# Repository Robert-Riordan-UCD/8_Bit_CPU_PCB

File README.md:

# 8-Bit PCB CPU

This is my version of [Ben Eaters 8-bit breadboard SAP-1 CPU](https://eater.net/8bit), converted to a PCB. I have made some minor changes as I could not find all of the components as listed in Ben's part list.

## Video of the computer running
https://youtube.com/shorts/QNcSWgcGv9o?si=QzoUVq9Kj8X1f4Rs

## Major Changes

### Random Access Memory

1. RAM IC's have been replaced with ATMega328-PU's. This should allow me to have persistant programs between power cycles.

## License

CERN Open Hardware Licence Version 2 - Permissive

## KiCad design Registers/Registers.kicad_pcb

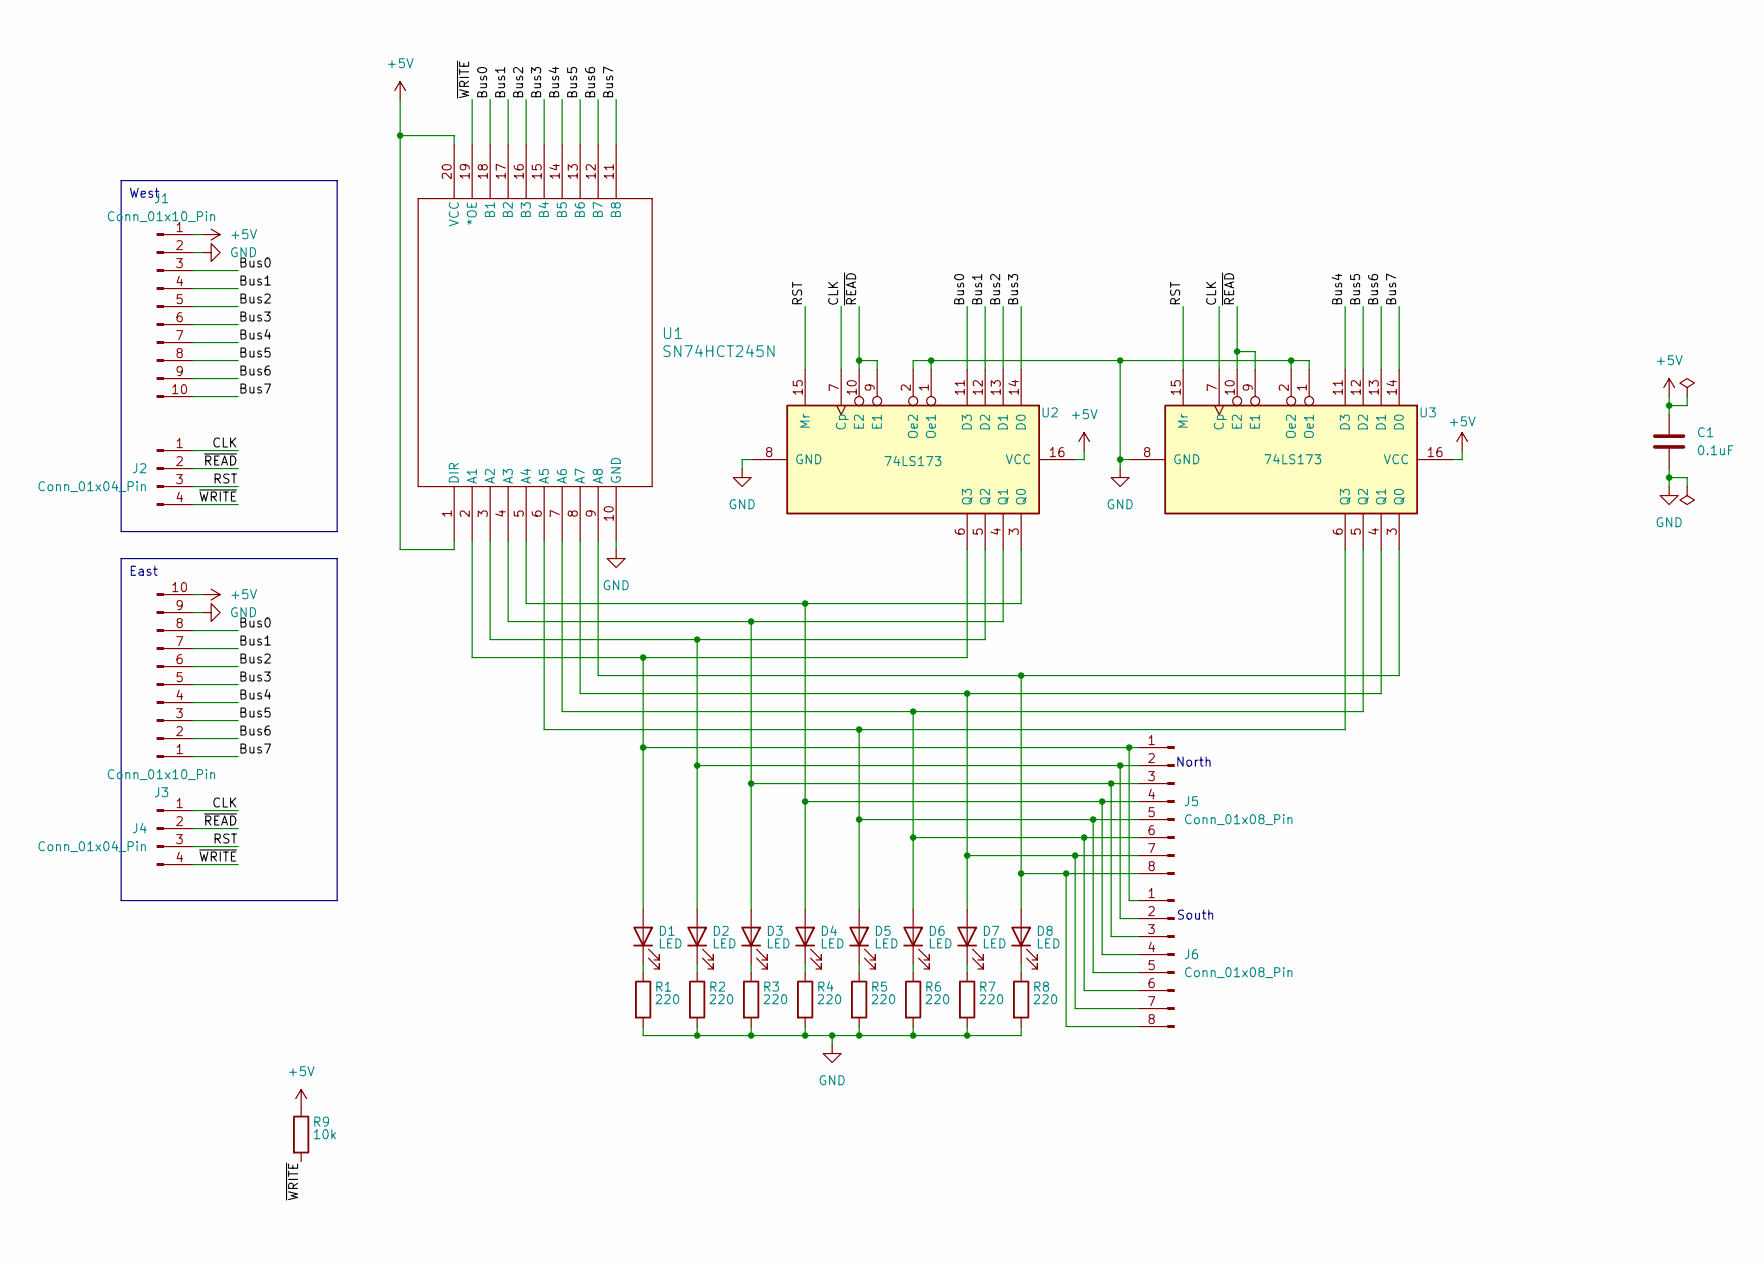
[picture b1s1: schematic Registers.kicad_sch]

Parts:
C1: 0.1uF; C_Disc_D5.0mm_W2.5mm_P2.50mm
D1, D2, D3, D4, D5, D6, D7, D8: LED; LED_D5.0mm
J1, J3: Conn_01x10_Pin; PinHeader_1x10_P2.54mm_Vertical
J2, J4: Conn_01x04_Pin; PinHeader_1x04_P2.54mm_Vertical
J5, J6: Conn_01x08_Pin; PinHeader_1x08_P2.54mm_Vertical
R1, R2, R3, R4, R5, R6, R7, R8: 220; CF_series_Resistors_THT
R9: 10k; CF_series_Resistors_THT
U1: SN74HCT245N; 8x_tristate_transceiver
U2, U3: 74LS173; DIP-16_W7.62mm

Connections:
+5V: C1.1, J1.1, J3.10, R9.1, U1.1 (DIR), U1.20 (VCC), U2.16 (VCC), U3.16 (VCC)
/Bus0: J1.3, J3.8, U1.18 (B1), U2.11 (D3)
/Bus1: J1.4, J3.7, U1.17 (B2), U2.12 (D2)
/Bus2: J1.5, J3.6, U1.16 (B3), U2.13 (D1)
/Bus3: J1.6, J3.5, U1.15 (B4), U2.14 (D0)
/Bus4: J1.7, J3.4, U1.14 (B5), U3.11 (D3)
/Bus5: J1.8, J3.3, U1.13 (B6), U3.12 (D2)
/Bus6: J1.9, J3.2, U1.12 (B7), U3.13 (D1)
/Bus7: J1.10, J3.1, U1.11 (B8), U3.14 (D0)
/CLK: J2.1, J4.1, U2.7 (Cp), U3.7 (Cp)
/RST: J2.3, J4.3, U2.15 (Mr), U3.15 (Mr)
/~READ: J2.2, J4.2, U2.9 (E1), U2.10 (E2), U3.9 (E1), U3.10 (E2)
/~WRITE: J2.4, J4.4, R9.2, U1.19 (*OE)
GND: C1.2, J1.2, J3.9, R1.2, R2.2, R3.2, R4.2, R5.2, R6.2, R7.2, R8.2, U1.10 (GND), U2.1 (Oe1), U2.2 (Oe2), U2.8 (GND), U3.1 (Oe1), U3.2 (Oe2), U3.8 (GND)
unnamed: D1.2 (A), J5.1, J6.1, U1.2 (A1), U2.6 (Q3)
unnamed: D1.1 (K), R1.1
unnamed: D2.2 (A), J5.2, J6.2, U1.3 (A2), U2.5 (Q2)
unnamed: D2.1 (K), R2.1
unnamed: D3.2 (A), J5.3, J6.3, U1.4 (A3), U2.4 (Q1)
unnamed: D3.1 (K), R3.1
unnamed: D4.2 (A), J5.4, J6.4, U1.5 (A4), U2.3 (Q0)
unnamed: D4.1 (K), R4.1
unnamed: D5.2 (A), J5.5, J6.5, U1.6 (A5), U3.6 (Q3)
unnamed: D5.1 (K), R5.1
unnamed: D6.2 (A), J5.6, J6.6, U1.7 (A6), U3.5 (Q2)
unnamed: D6.1 (K), R6.1
unnamed: D7.2 (A), J5.7, J6.7, U1.8 (A7), U3.4 (Q1)
unnamed: D7.1 (K), R7.1
unnamed: D8.2 (A), J5.8, J6.8, U1.9 (A8), U3.3 (Q0)
unnamed: D8.1 (K), R8.1

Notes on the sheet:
West
East
North
South

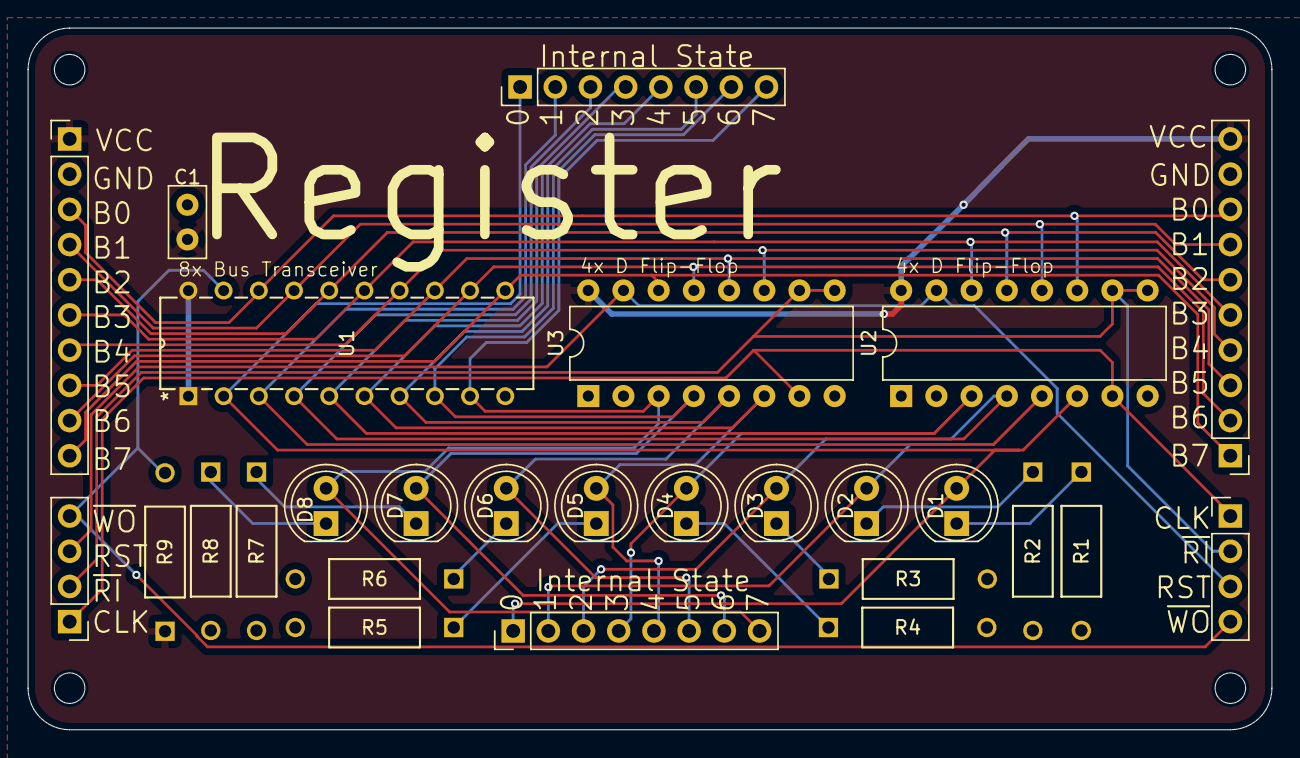
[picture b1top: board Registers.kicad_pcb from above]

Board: 2 copper layers, 89.8 x 50.6 mm, 27 parts (0 on the bottom side), 30 nets.

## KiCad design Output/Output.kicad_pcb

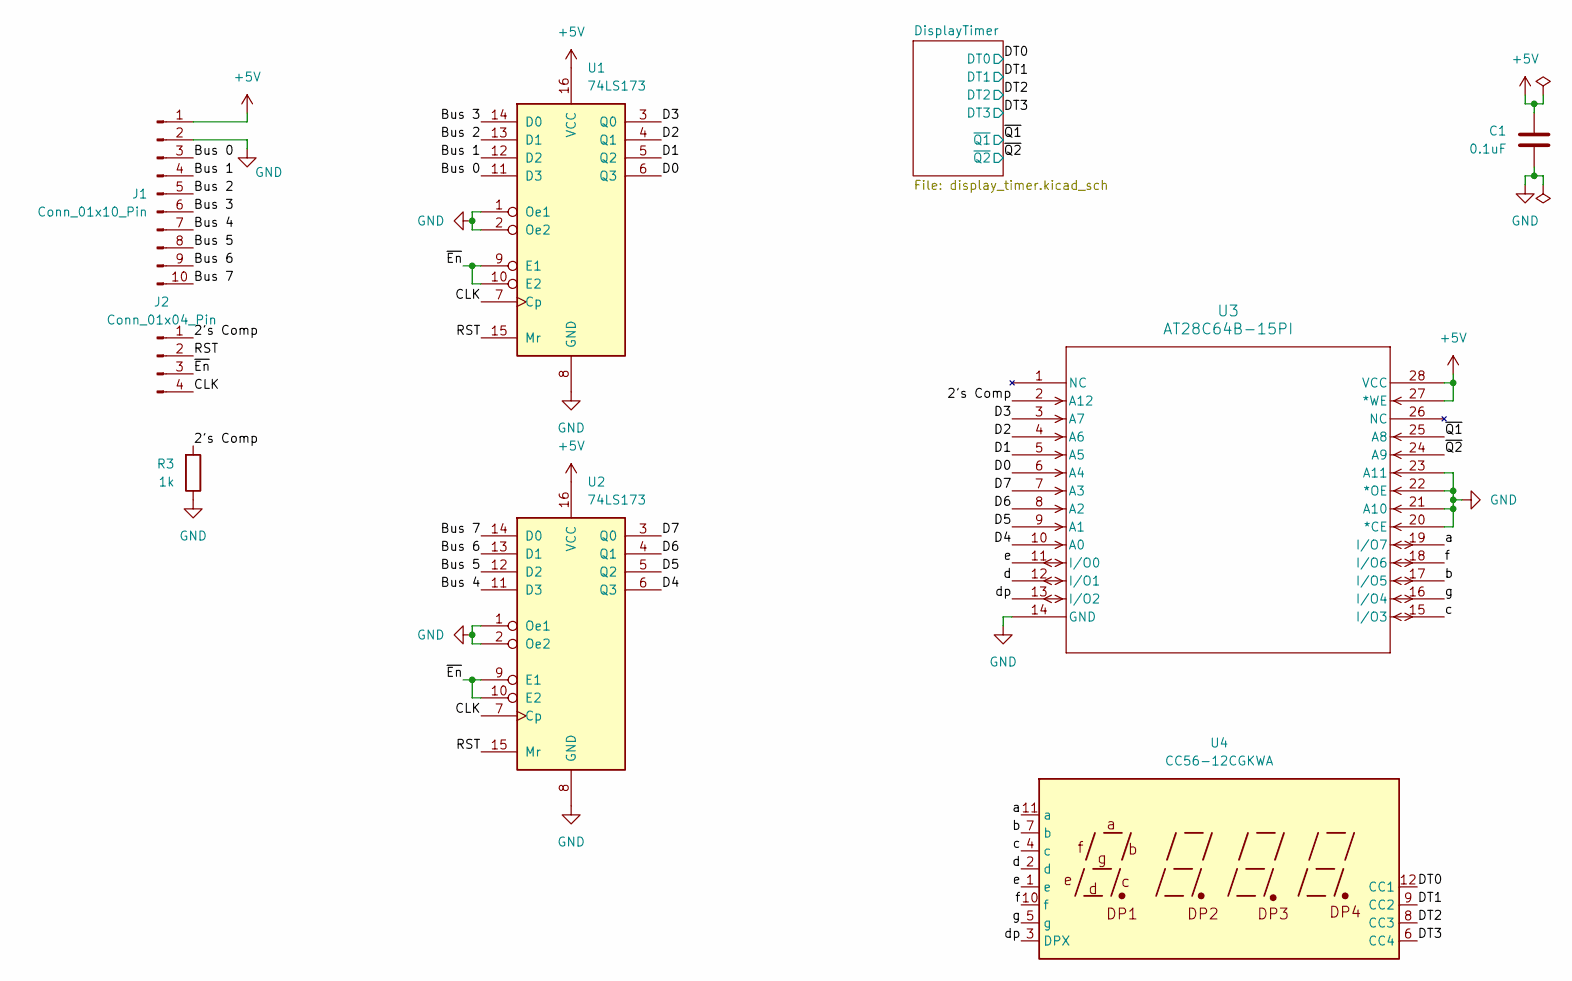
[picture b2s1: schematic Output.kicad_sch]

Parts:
C1: 0.1uF; C_Disc_D5.0mm_W2.5mm_P2.50mm
J1: Conn_01x10_Pin; PinHeader_1x10_P2.54mm_Vertical
J2: Conn_01x04_Pin; PinHeader_1x04_P2.54mm_Vertical
R3: 1k; CF_series_Resistors_THT
U1, U2: 74LS173; DIP-16_W7.62mm
U3: AT28C64B-15PI; eeprom
U4: CC56-12CGKWA; CA56-12CGKWA

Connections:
+5V: C1.1, J1.1, U1.16 (VCC), U2.16 (VCC), U3.27 (*WE), U3.28 (VCC); also elsewhere on the board
/2's Comp: J2.1, R3.2, U3.2 (A12)
/Bus 0: J1.3, U1.11 (D3)
/Bus 1: J1.4, U1.12 (D2)
/Bus 2: J1.5, U1.13 (D1)
/Bus 3: J1.6, U1.14 (D0)
/Bus 4: J1.7, U2.11 (D3)
/Bus 5: J1.8, U2.12 (D2)
/Bus 6: J1.9, U2.13 (D1)
/Bus 7: J1.10, U2.14 (D0)
/CLK: J2.4, U1.7 (Cp), U2.7 (Cp)
/D0: U1.6 (Q3), U3.6 (A4)
/D1: U1.5 (Q2), U3.5 (A5)
/D2: U1.4 (Q1), U3.4 (A6)
/D3: U1.3 (Q0), U3.3 (A7)
/D4: U2.6 (Q3), U3.10 (A0)
/D5: U2.5 (Q2), U3.9 (A1)
/D6: U2.4 (Q1), U3.8 (A2)
/D7: U2.3 (Q0), U3.7 (A3)
/DT0: U4.12 (CC1); also elsewhere on the board
/DT1: U4.9 (CC2); also elsewhere on the board
/DT2: U4.8 (CC3); also elsewhere on the board
/DT3: U4.6 (CC4); also elsewhere on the board
/RST: J2.2, U1.15 (Mr), U2.15 (Mr)
/a: U3.19 (I/O7), U4.11 (a)
/b: U3.17 (I/O5), U4.7 (b)
/c: U3.15 (I/O3), U4.4 (c)
/d: U3.12 (I/O1), U4.2 (d)
/dp: U3.13 (I/O2), U4.3 (DPX)
/e: U3.11 (I/O0), U4.1 (e)
/f: U3.18 (I/O6), U4.10 (f)
/g: U3.16 (I/O4), U4.5 (g)
/~En: J2.3, U1.9 (E1), U1.10 (E2), U2.9 (E1), U2.10 (E2)
/~Q1: U3.25 (A8); also elsewhere on the board
/~Q2: U3.24 (A9); also elsewhere on the board
GND: C1.2, J1.2, R3.1, U1.1 (Oe1), U1.2 (Oe2), U1.8 (GND), U2.1 (Oe1), U2.2 (Oe2), U2.8 (GND), U3.14 (GND), U3.20 (*CE), U3.21 (A10), U3.22 (*OE), U3.23 (A11); also elsewhere on the board

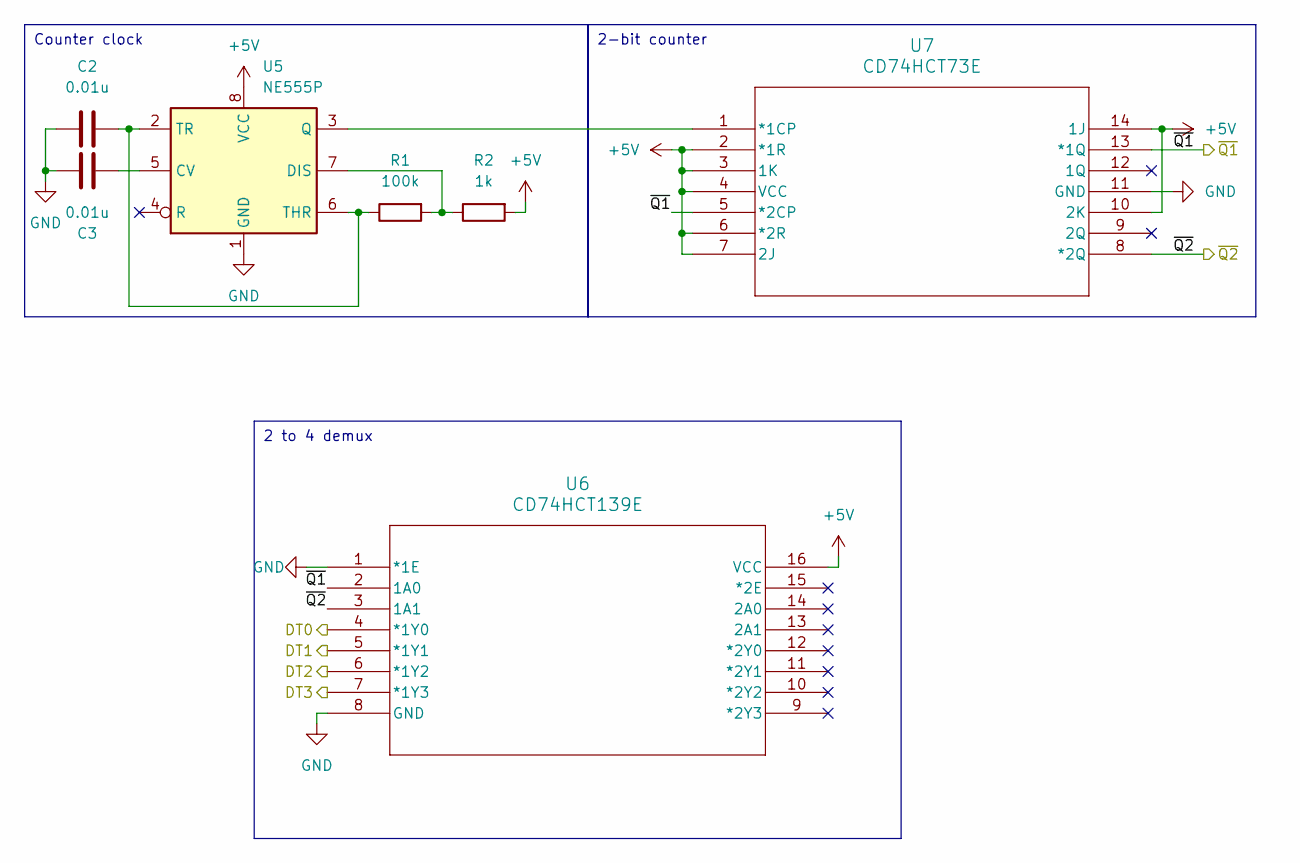
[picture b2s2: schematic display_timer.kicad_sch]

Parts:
C2, C3: 0.01u; C_Disc_D5.0mm_W2.5mm_P2.50mm
R1: 100k; CF_series_Resistors_THT
R2: 1k; CF_series_Resistors_THT
U5: NE555P; DIP-8_W7.62mm
U6: CD74HCT139E; 2x_2_to_4_demux
U7: CD74HCT73E; 2x_JK_FF

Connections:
+5V: R2.2, U5.8 (VCC), U6.16 (VCC), U7.2 (*1R), U7.3 (1K), U7.4 (VCC), U7.6 (*2R), U7.7 (2J), U7.10 (2K), U7.14 (1J); also elsewhere on the board
/DT0: U6.4 (*1Y0); also elsewhere on the board
/DT1: U6.5 (*1Y1); also elsewhere on the board
/DT2: U6.6 (*1Y2); also elsewhere on the board
/DT3: U6.7 (*1Y3); also elsewhere on the board
/~Q1: U6.2 (1A0), U7.5 (*2CP), U7.13 (*1Q); also elsewhere on the board
/~Q2: U6.3 (1A1), U7.8 (*2Q); also elsewhere on the board
GND: C2.1, C3.1, U5.1 (GND), U6.1 (*1E), U6.8 (GND), U7.11 (GND); also elsewhere on the board
unnamed: C3.2, U5.5 (CV)
unnamed: R1.2, R2.1, U5.7 (DIS)
unnamed: U5.3 (Q), U7.1 (*1CP)
unnamed: C2.2, R1.1, U5.2 (TR), U5.6 (THR)

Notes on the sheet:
2 to 4 demux
Counter clock
2-bit counter

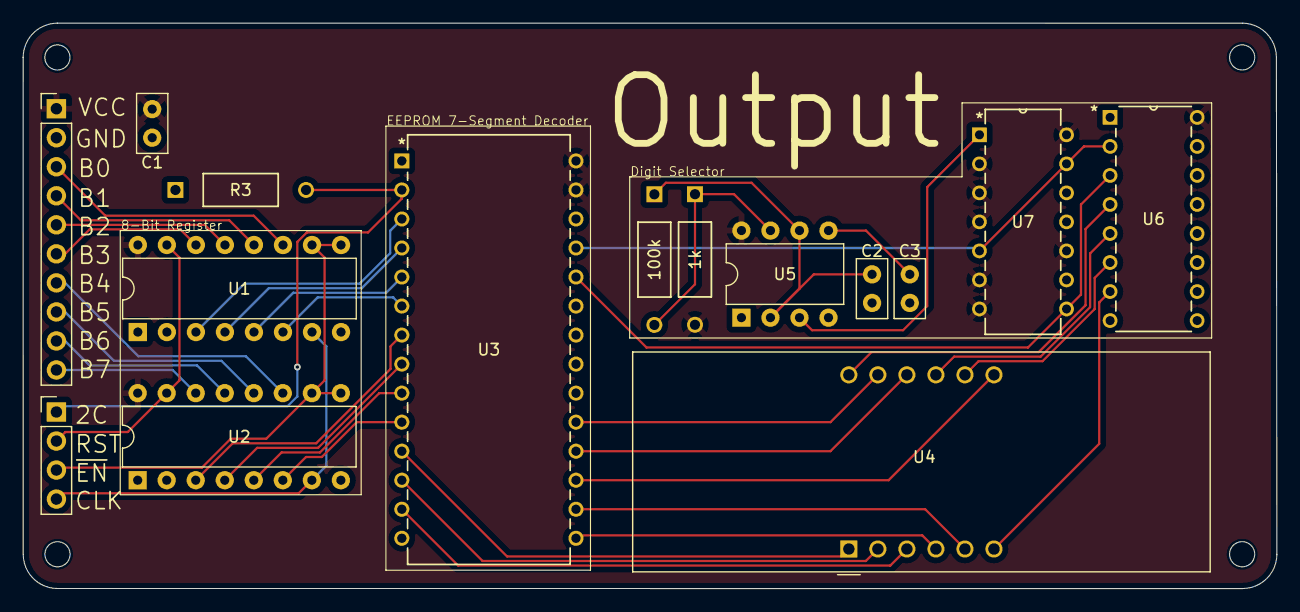
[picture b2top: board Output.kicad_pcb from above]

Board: 2 copper layers, 109.7 x 49.5 mm, 15 parts (0 on the bottom side), 40 nets.

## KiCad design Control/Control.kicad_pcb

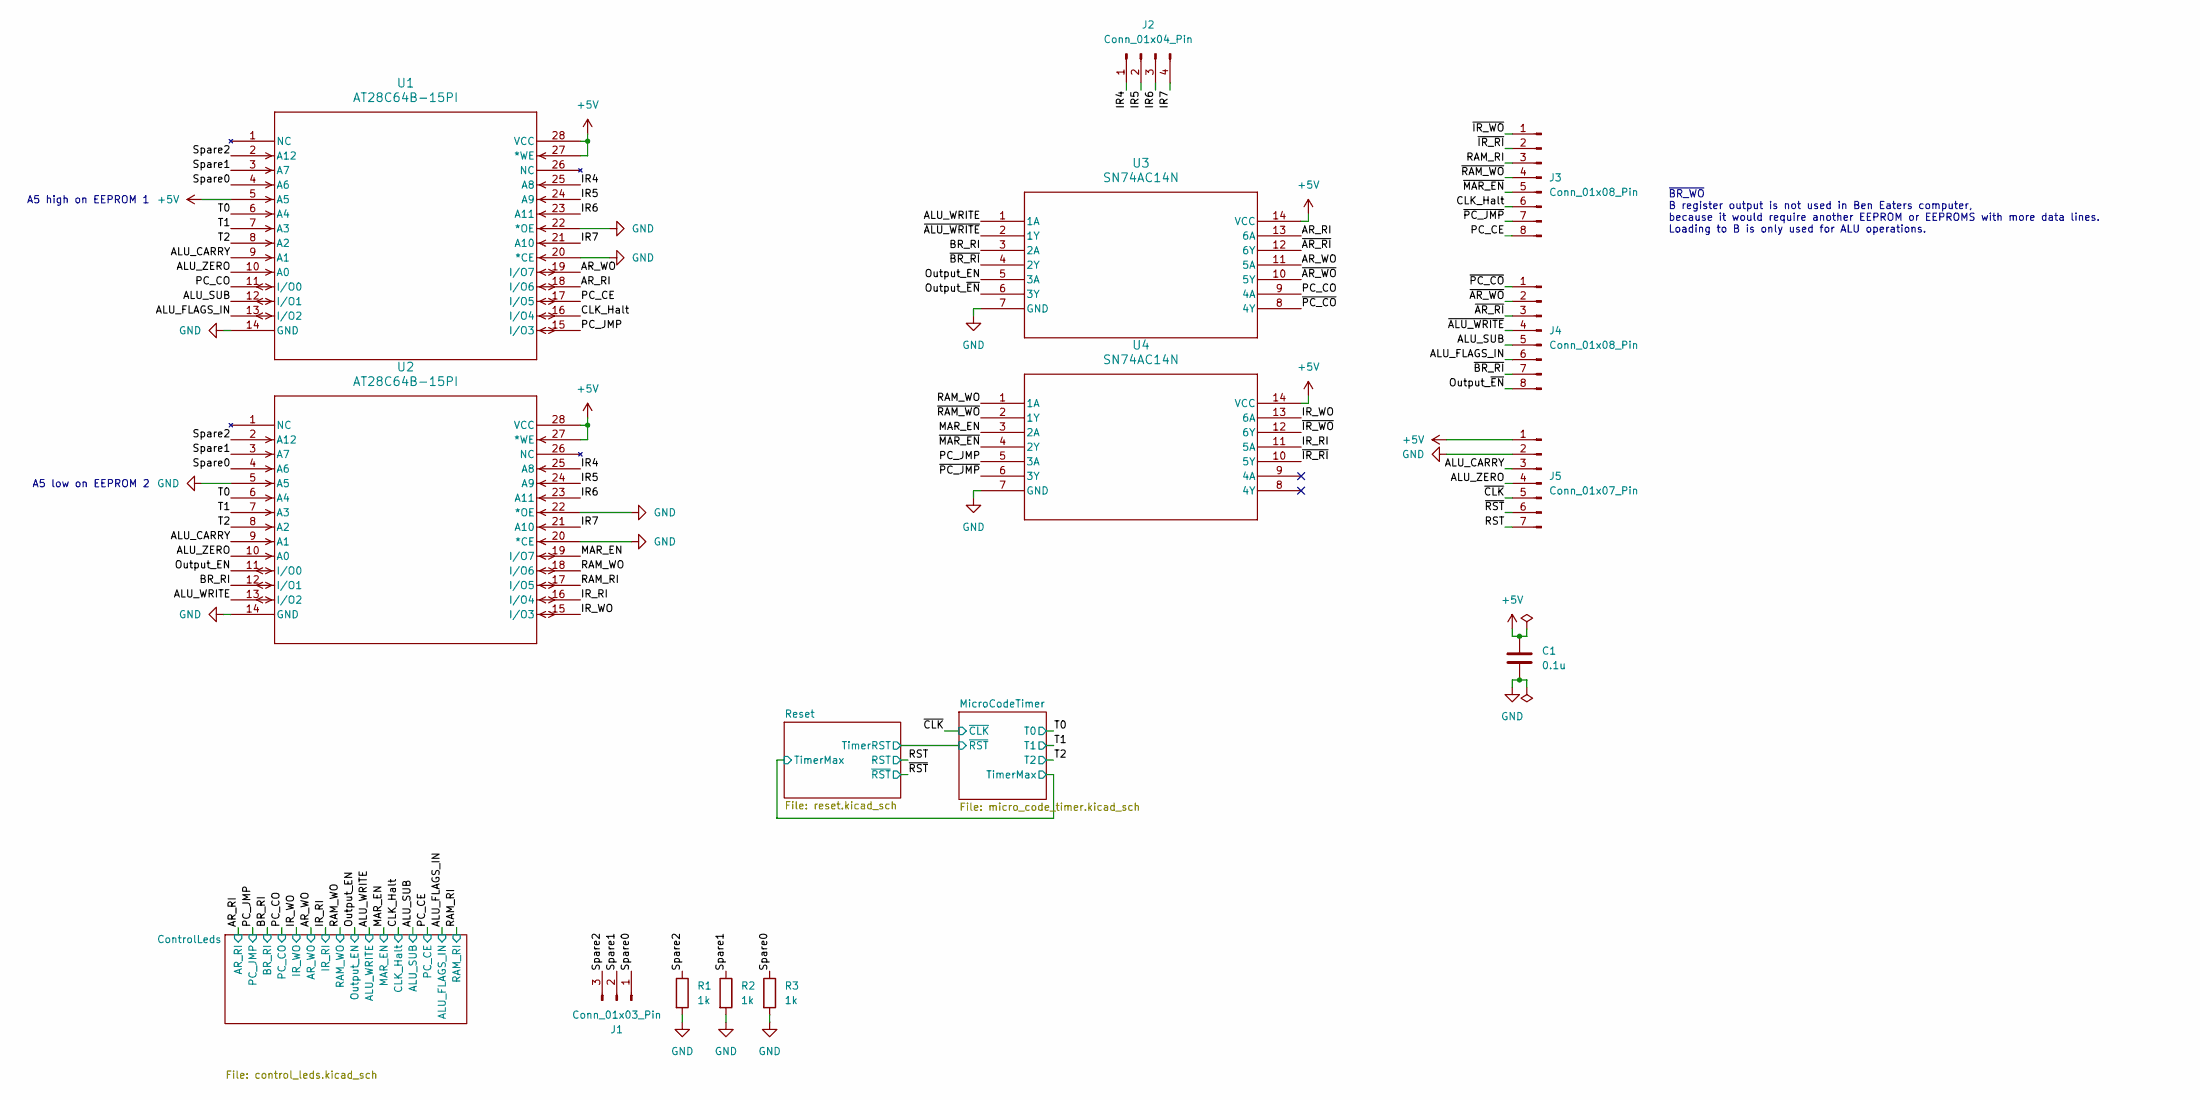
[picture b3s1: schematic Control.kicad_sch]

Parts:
C1: 0.1u; C_Disc_D5.0mm_W2.5mm_P2.50mm
J1: Conn_01x03_Pin; PinHeader_1x03_P2.54mm_Vertical
J2: Conn_01x04_Pin; PinHeader_1x04_P2.54mm_Vertical
J3, J4: Conn_01x08_Pin; PinHeader_1x08_P2.54mm_Vertical
J5: Conn_01x07_Pin; PinHeader_1x07_P2.54mm_Vertical
R1, R2, R3: 1k; CF_series_Resistors_THT
U1, U2: AT28C64B-15PI; eeprom
U3, U4: SN74AC14N; 6x_not

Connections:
+5V: C1.1, J5.1, U1.5 (A5), U1.27 (*WE), U1.28 (VCC), U2.27 (*WE), U2.28 (VCC), U3.14 (VCC), U4.14 (VCC); also elsewhere on the board
/ALU_CARRY: J5.3, U1.9 (A1), U2.9 (A1)
/ALU_FLAGS_IN: J4.6, U1.13 (I/O2); also elsewhere on the board
/ALU_SUB: J4.5, U1.12 (I/O1); also elsewhere on the board
/ALU_WRITE: U2.13 (I/O2), U3.1 (1A); also elsewhere on the board
/ALU_ZERO: J5.4, U1.10 (A0), U2.10 (A0)
/AR_RI: U1.18 (I/O6), U3.13 (6A); also elsewhere on the board
/AR_WO: U1.19 (I/O7), U3.11 (5A); also elsewhere on the board
/BR_RI: U2.12 (I/O1), U3.3 (2A); also elsewhere on the board
/CLK_Halt: J3.6, U1.16 (I/O4); also elsewhere on the board
/IR4: J2.1, U1.25 (A8), U2.25 (A8)
/IR5: J2.2, U1.24 (A9), U2.24 (A9)
/IR6: J2.3, U1.23 (A11), U2.23 (A11)
/IR7: J2.4, U1.21 (A10), U2.21 (A10)
/IR_RI: U2.16 (I/O4), U4.11 (5A); also elsewhere on the board
/IR_WO: U2.15 (I/O3), U4.13 (6A); also elsewhere on the board
/MAR_EN: U2.19 (I/O7), U4.3 (2A); also elsewhere on the board
/Output_EN: U2.11 (I/O0), U3.5 (3A); also elsewhere on the board
/Output_~EN: J4.8, U3.6 (3Y)
/PC_CE: J3.8, U1.17 (I/O5); also elsewhere on the board
/PC_CO: U1.11 (I/O0), U3.9 (4A); also elsewhere on the board
/PC_JMP: U1.15 (I/O3), U4.5 (3A); also elsewhere on the board
/RAM_RI: J3.3, U2.17 (I/O5); also elsewhere on the board
/RAM_WO: U2.18 (I/O6), U4.1 (1A); also elsewhere on the board
/RST: J5.7; also elsewhere on the board
/Spare0: J1.1, R3.1, U1.4 (A6), U2.4 (A6)
/Spare1: J1.2, R2.1, U1.3 (A7), U2.3 (A7)
/Spare2: J1.3, R1.1, U1.2 (A12), U2.2 (A12)
/T0: U1.6 (A4), U2.6 (A4); also elsewhere on the board
/T1: U1.7 (A3), U2.7 (A3); also elsewhere on the board
/T2: U1.8 (A2), U2.8 (A2); also elsewhere on the board
/~ALU_WRITE: J4.4, U3.2 (1Y)
/~AR_RI: J4.3, U3.12 (6Y)
/~AR_WO: J4.2, U3.10 (5Y)
/~BR_RI: J4.7, U3.4 (2Y)
/~CLK: J5.5; also elsewhere on the board
/~IR_RI: J3.2, U4.10 (5Y)
/~IR_WO: J3.1, U4.12 (6Y)
/~MAR_EN: J3.5, U4.4 (2Y)
/~PC_CO: J4.1, U3.8 (4Y)
/~PC_JMP: J3.7, U4.6 (3Y)
/~RAM_WO: J3.4, U4.2 (1Y)
/~RST: J5.6; also elsewhere on the board
GND: C1.2, J5.2, R1.2, R2.2, R3.2, U1.14 (GND), U1.20 (*CE), U1.22 (*OE), U2.5 (A5), U2.14 (GND), U2.20 (*CE), U2.22 (*OE), U3.7 (GND), U4.7 (GND); also elsewhere on the board

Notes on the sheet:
A5 high on EEPROM 1
~{BR_WO} B register output is not used in Ben Eaters computer, because it would require another EEPROM or EEPROMS with more data lines. Loading to B is only used for ALU operations.
A5 low on EEPROM 2

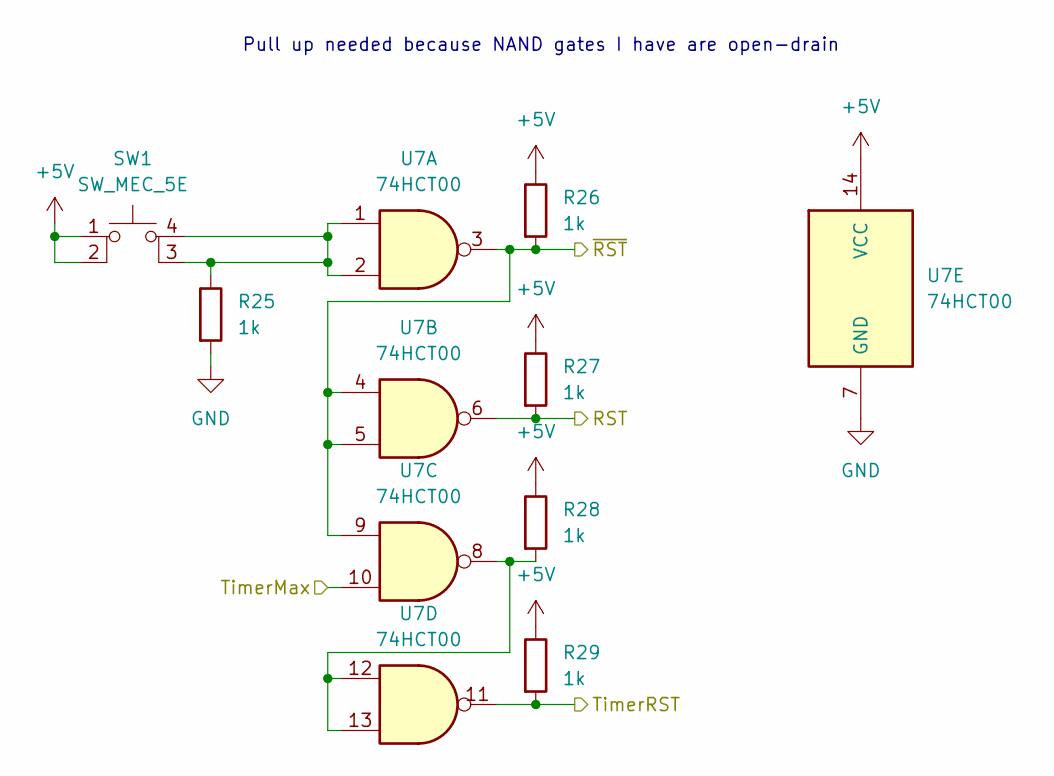
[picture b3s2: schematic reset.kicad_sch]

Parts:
R25, R26, R27, R28, R29: 1k; CF_series_Resistors_THT
SW1: SW_MEC_5E; tactile_switch
U7: 74HCT00; DIP-14_W7.62mm

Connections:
+5V: R26.1, R27.1, R28.1, R29.1, SW1.1, SW1.2, U7.14 (VCC); also elsewhere on the board
/MicroCodeTimer/TimerMax: U7.10; also elsewhere on the board
/MicroCodeTimer/~RST: R29.2, U7.11; also elsewhere on the board
/RST: R27.2, U7.6; also elsewhere on the board
/~RST: R26.2, U7.3, U7.4, U7.5, U7.9; also elsewhere on the board
GND: R25.2, U7.7 (GND); also elsewhere on the board
unnamed: R28.2, U7.8, U7.12, U7.13
unnamed: R25.1, SW1.3 (K), SW1.4 (A), U7.1, U7.2

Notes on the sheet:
Pull up needed because NAND gates I have are open-drain

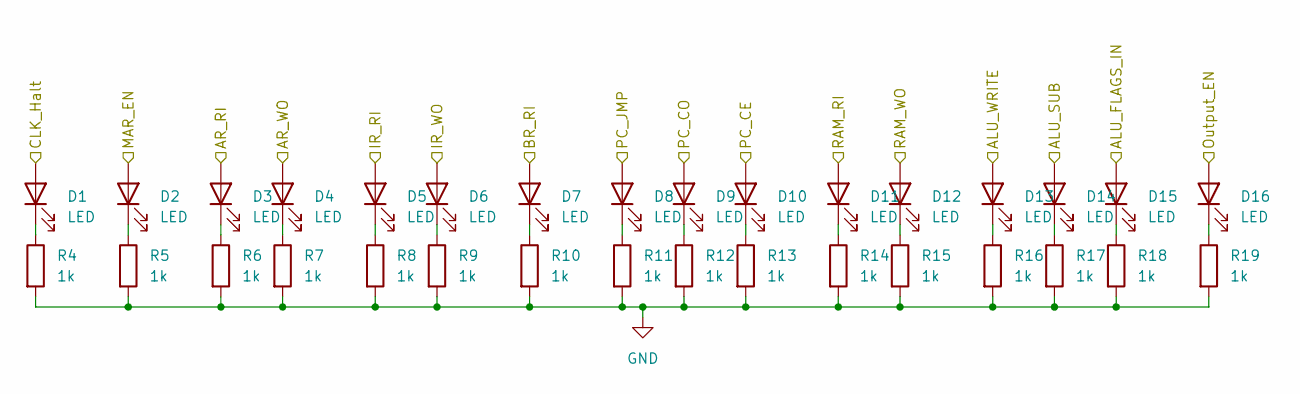
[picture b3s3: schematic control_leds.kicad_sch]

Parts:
D1, D2, D3, D4, D5, D6, D7, D8, D9, D10, D11, D12, D13, D14, D15, D16: LED; LED_D5.0mm
R4, R5, R6, R7, R8, R9, R10, R11, R12, R13, R14, R15, R16, R17, R18, R19: 1k; CF_series_Resistors_THT

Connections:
/ALU_FLAGS_IN: D15.2 (A); also elsewhere on the board
/ALU_SUB: D14.2 (A); also elsewhere on the board
/ALU_WRITE: D13.2 (A); also elsewhere on the board
/AR_RI: D3.2 (A); also elsewhere on the board
/AR_WO: D4.2 (A); also elsewhere on the board
/BR_RI: D7.2 (A); also elsewhere on the board
/CLK_Halt: D1.2 (A); also elsewhere on the board
/IR_RI: D5.2 (A); also elsewhere on the board
/IR_WO: D6.2 (A); also elsewhere on the board
/MAR_EN: D2.2 (A); also elsewhere on the board
/Output_EN: D16.2 (A); also elsewhere on the board
/PC_CE: D10.2 (A); also elsewhere on the board
/PC_CO: D9.2 (A); also elsewhere on the board
/PC_JMP: D8.2 (A); also elsewhere on the board
/RAM_RI: D11.2 (A); also elsewhere on the board
/RAM_WO: D12.2 (A); also elsewhere on the board
GND: R4.2, R5.2, R6.2, R7.2, R8.2, R9.2, R10.2, R11.2, R12.2, R13.2, R14.2, R15.2, R16.2, R17.2, R18.2, R19.2; also elsewhere on the board
unnamed: D1.1 (K), R4.1
unnamed: D2.1 (K), R5.1
unnamed: D3.1 (K), R6.1
unnamed: D4.1 (K), R7.1
unnamed: D5.1 (K), R8.1
unnamed: D6.1 (K), R9.1
unnamed: D7.1 (K), R10.1
unnamed: D8.1 (K), R11.1
unnamed: D9.1 (K), R12.1
unnamed: D10.1 (K), R13.1
unnamed: D11.1 (K), R14.1
unnamed: D12.1 (K), R15.1
unnamed: D13.1 (K), R16.1
unnamed: D14.1 (K), R17.1
unnamed: D15.1 (K), R18.1
unnamed: D16.1 (K), R19.1

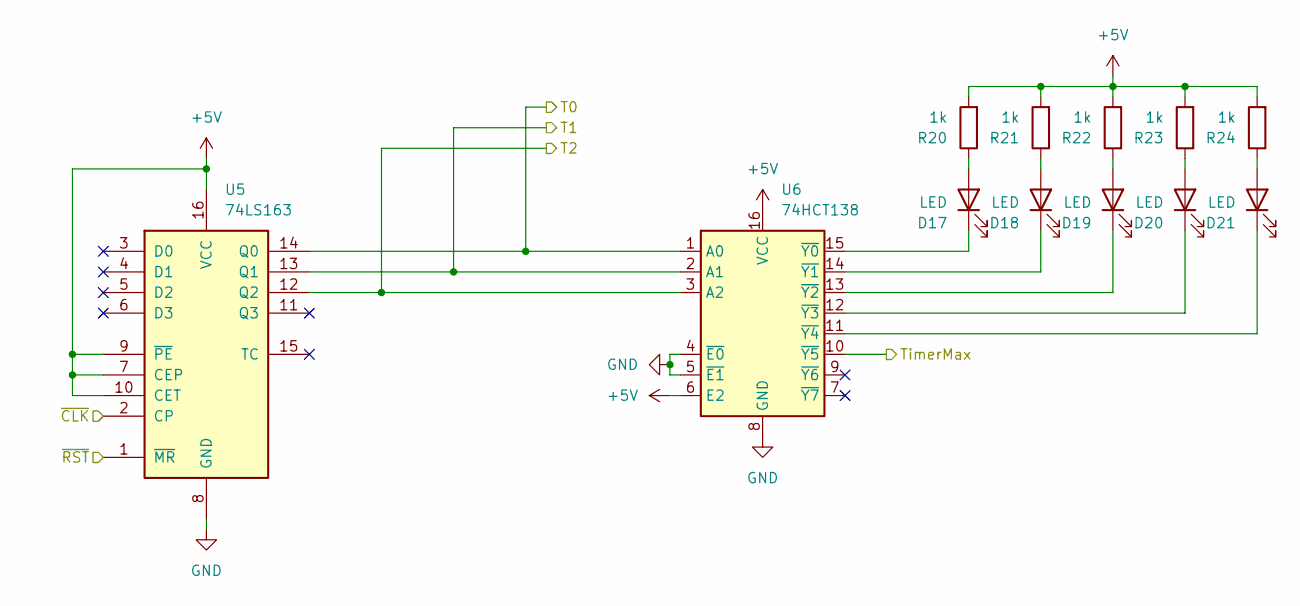
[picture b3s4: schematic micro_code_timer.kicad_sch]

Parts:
D17, D18, D19, D20, D21: LED; LED_D5.0mm
R20, R21, R22, R23, R24: 1k; CF_series_Resistors_THT
U5: 74LS163; DIP-16_W7.62mm
U6: 74HCT138; DIP-16_W7.62mm

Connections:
+5V: R20.2, R21.2, R22.2, R23.2, R24.2, U5.7 (CEP), U5.9 (~PE), U5.10 (CET), U5.16 (VCC), U6.6 (E2), U6.16 (VCC); also elsewhere on the board
/MicroCodeTimer/TimerMax: U6.10 (~Y5); also elsewhere on the board
/MicroCodeTimer/~RST: U5.1 (~MR); also elsewhere on the board
/T0: U5.14 (Q0), U6.1 (A0); also elsewhere on the board
/T1: U5.13 (Q1), U6.2 (A1); also elsewhere on the board
/T2: U5.12 (Q2), U6.3 (A2); also elsewhere on the board
/~CLK: U5.2 (CP); also elsewhere on the board
GND: U5.8 (GND), U6.4 (~E0), U6.5 (~E1), U6.8 (GND); also elsewhere on the board
unnamed: D17.2 (A), R20.1
unnamed: D17.1 (K), U6.15 (~Y0)
unnamed: D18.2 (A), R21.1
unnamed: D18.1 (K), U6.14 (~Y1)
unnamed: D19.2 (A), R22.1
unnamed: D19.1 (K), U6.13 (~Y2)
unnamed: D20.2 (A), R23.1
unnamed: D20.1 (K), U6.12 (~Y3)
unnamed: D21.2 (A), R24.1
unnamed: D21.1 (K), U6.11 (~Y4)

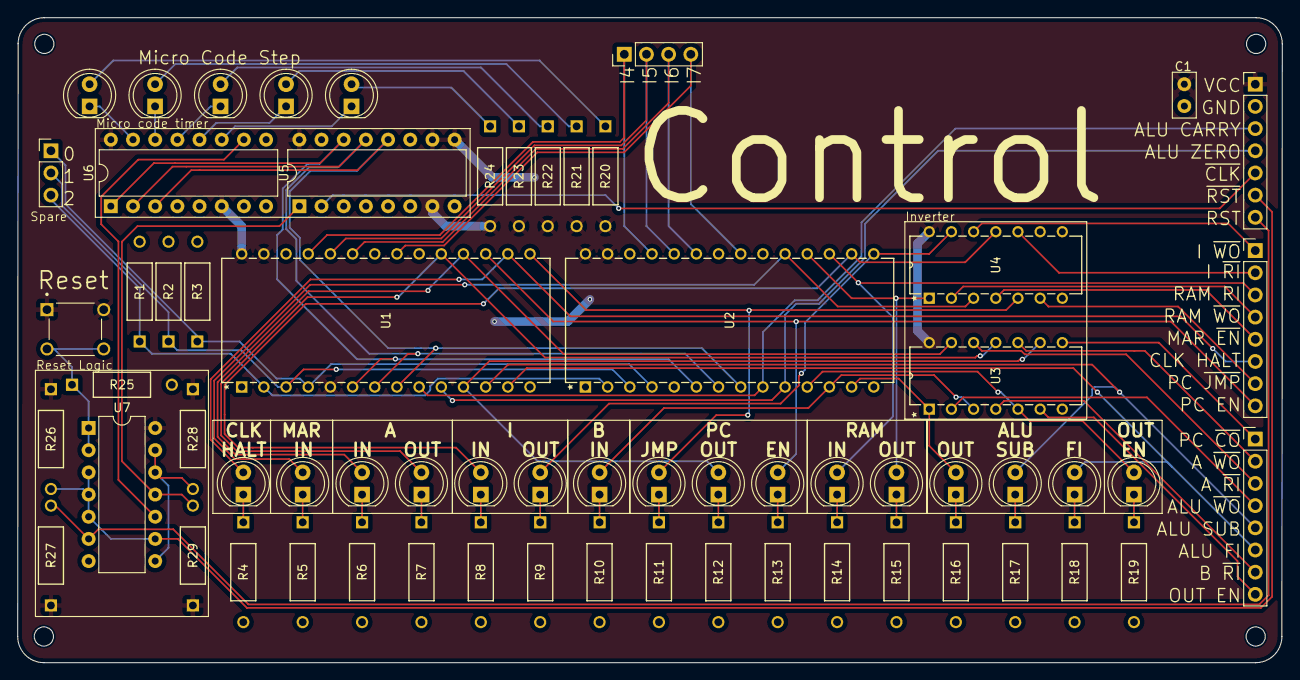
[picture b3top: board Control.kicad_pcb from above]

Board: 2 copper layers, 144.8 x 73.9 mm, 64 parts (0 on the bottom side), 74 nets.
